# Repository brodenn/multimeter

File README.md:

# 🧪 Arduino Multimeter Project

This is my school project where I designed, built, and programmed a fully functional digital multimeter using an Arduino Uno and a custom PCB designed in KiCad.

📄 [Click here to read the full report (PDF)](docs/P2-Multimeter-Report.pdf)

---

## ✅ Features

- 🟢 **Voltage Measurement**
  - Low voltage: 0–5V (direct to ADC)
  - High voltage: 5–33.7V (via voltage divider)

- 🟠 **Resistance Measurement**
  - Low resistance: 0–1kΩ
  - High resistance: 1–100kΩ

- 🔋 **Battery Monitoring**
  - Detects 9V and 12V sources
  - Provides low battery and no battery warnings

- 🎛️ **Rotary Switch Mode Selection**
  - Modes detected via 4-bit digital input

- 🔊 **Visual & Audio Feedback**
  - Green/Yellow/Red LEDs for status indication
  - Buzzer for continuity and battery alerts

- 🔢 **3-Digit 7-Segment Display**
  - Controlled via CD74HCT4511 BCD driver
  - Efficient multiplexing with decimal control

---

## 📷 Preview

### Schematic

### Top Layer

### Bottom Layer

### PCB Design

### Assembled Multimeter

---

## 🛠️ Tools Used

- Arduino Uno R3
- KiCad 7+
- LTspice (for simulation)
- Fluke multimeter (for verification)
- Soldering station, protoboard, and banana connectors

---

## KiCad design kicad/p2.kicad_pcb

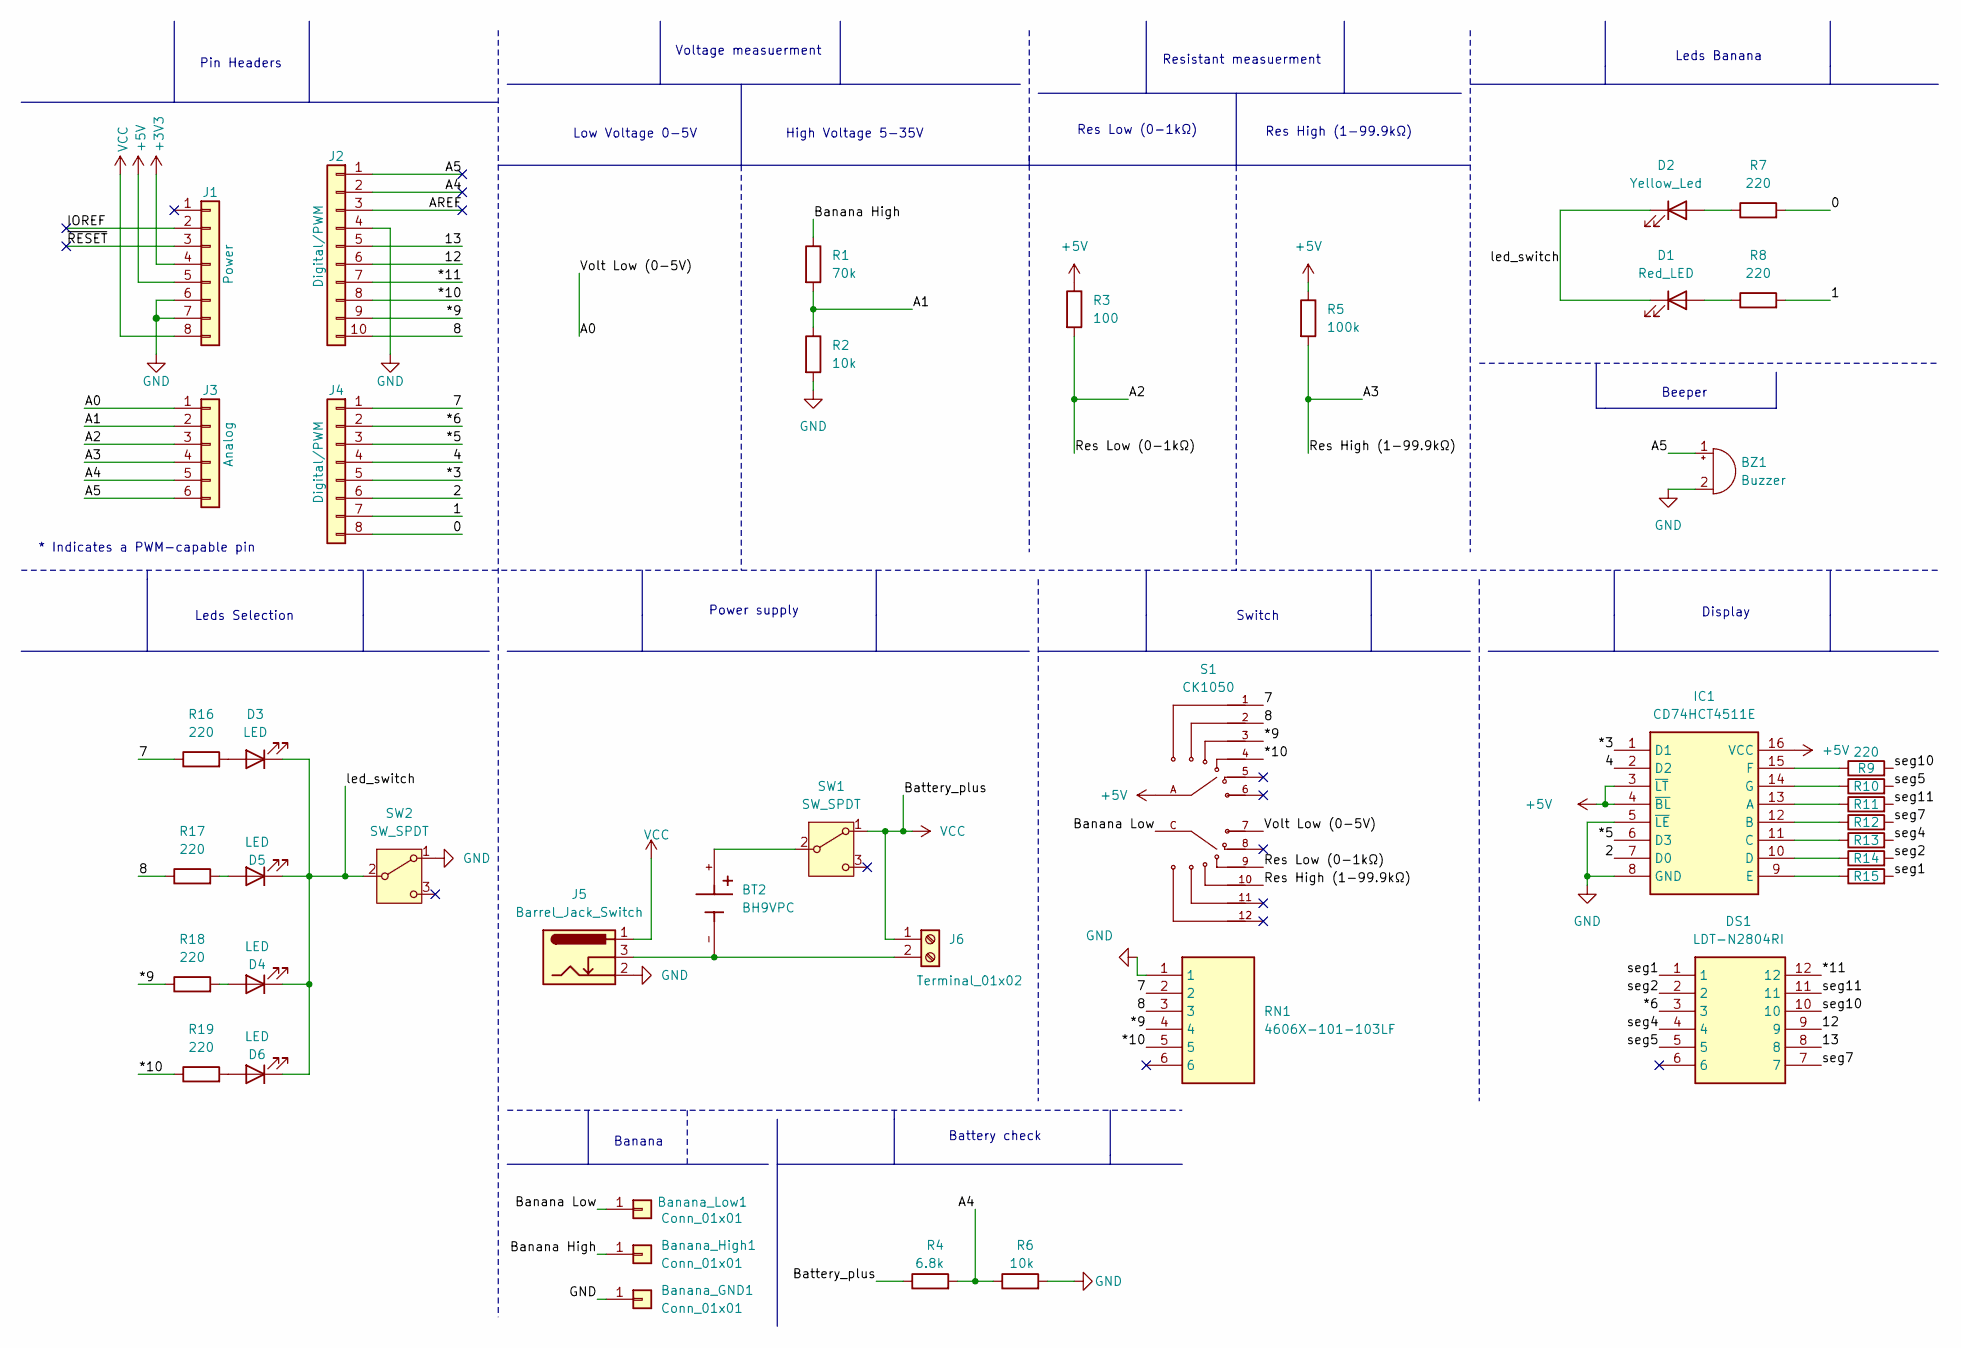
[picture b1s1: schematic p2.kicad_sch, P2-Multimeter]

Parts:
BT2: BH9VPC; BAT_BH9VPC; PARTREV F
BZ1: Buzzer; Buzzer_12x9.5RM7.6
Banana_GND1: Conn_01x01; Banana_Jack_1Pin
Banana_High1: Conn_01x01; Banana_Jack_1Pin
Banana_Low1: Conn_01x01; Banana_Jack_1Pin
D1: Red_LED; LED_D5.0mm
D2: Yellow_Led; LED_D5.0mm
D3, D4, D5, D6: LED; LED_D5.0mm
DS1: LDT-N2804RI; DIPS762W45P254L2253H610Q12N; Mouser Part Number 696-LDT-N2804RI
IC1: CD74HCT4511E; DIP794W53P254L1930H508Q16N; Mouser Part Number 595-CD74HCT4511E
J1: Power; PinSocket_1x08_P2.54mm_Vertical
J2: Digital/PWM; PinSocket_1x10_P2.54mm_Vertical
J3: Analog; PinSocket_1x06_P2.54mm_Vertical
J4: Digital/PWM; PinSocket_1x08_P2.54mm_Vertical
J5: Barrel_Jack_Switch; BarrelJack_Horizontal
J6: Terminal_01x02; terminal_battery
R1: 70k; R_Axial_DIN0207_L6.3mm_D2.5mm_P10.16mm_Horizontal
R2, R6: 10k; R_Axial_DIN0207_L6.3mm_D2.5mm_P10.16mm_Horizontal
R3: 100; R_Axial_DIN0207_L6.3mm_D2.5mm_P10.16mm_Horizontal
R4: 6.8k; R_Axial_DIN0207_L6.3mm_D2.5mm_P10.16mm_Horizontal
R5: 100k; R_Axial_DIN0207_L6.3mm_D2.5mm_P10.16mm_Horizontal
R7, R8, R9, R10, R11, R12, R13, R14, R15, R16, R17, R18, R19: 220; R_Axial_DIN0207_L6.3mm_D2.5mm_P10.16mm_Horizontal
RN1: 4606X-101-103LF; 4606X102103LF; Mouser Part Number 652-4606X-1LF-10K
S1: CK1050; SW_CK1050; PARTREV NA
SW1, SW2: SW_SPDT; SW_Slide-03_Wuerth-WS-SLTV_10x2.5x6.4_P2.54mm

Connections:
+3V3: J1.4
+5V: IC1.3 (~LT), IC1.4 (~BL), IC1.16 (VCC), J1.5, R3.1, R5.1, S1.A
/0: J4.8, R7.2
/1: J4.7, R8.2
/2: IC1.7 (D0), J4.6
/4: IC1.2 (D2), J4.4
/7: J4.1, R16.1, RN1.2, S1.1
/8: J2.10, R17.1, RN1.3, S1.2
/12: DS1.9, J2.6
/13: DS1.8, J2.5
/*3: IC1.1 (D1), J4.5
/*5: IC1.6 (D3), J4.3
/*6: DS1.3, J4.2
/*9: J2.9, R18.1, RN1.4, S1.3
/*10: J2.8, R19.1, RN1.5, S1.4
/*11: DS1.12, J2.7
/A0: J3.1, S1.7
/A1: J3.2, R1.2, R2.1
/A2: J3.3, R3.2, S1.9
/A3: J3.4, R5.2, S1.10
/A4: J2.2, J3.5, R4.2, R6.1
/A5: BZ1.1 (+), J2.1, J3.6
/AREF: J2.3
/Banana High: Banana_High1.1, R1.1
/Banana Low: Banana_Low1.1, S1.C
/IOREF: J1.2
/led_switch: D1.1 (K), D2.1 (K), D3.1 (K), D4.1 (K), D5.1 (K), D6.1 (K), SW2.2 (B)
/seg1: DS1.1, R15.2
/seg2: DS1.2, R14.2
/seg4: DS1.4, R13.2
/seg5: DS1.5, R10.2
/seg7: DS1.7, R12.2
/seg10: DS1.10, R9.2
/seg11: DS1.11, R11.2
/~RESET: J1.3
GND: BZ1.2 (-), Banana_GND1.1, IC1.5 (~LE), IC1.8 (GND), J1.6, J1.7, J2.4, J5.2, R2.2, R6.2, RN1.1, SW2.1 (A)
unnamed: D1.2 (A), R8.1
unnamed: D2.2 (A), R7.1
unnamed: D3.2 (A), R16.2
unnamed: D4.2 (A), R18.2
unnamed: D5.2 (A), R17.2
unnamed: D6.2 (A), R19.2
unnamed: IC1.13 (A), R11.1
unnamed: IC1.12 (B), R12.1
unnamed: IC1.11 (C), R13.1
unnamed: IC1.10 (D), R14.1
unnamed: IC1.9 (E), R15.1
unnamed: IC1.15 (F), R9.1
unnamed: IC1.14 (G), R10.1
unnamed: BT2.-, J5.3, J6.2
unnamed: BT2.+, SW1.2 (B)
VCC: J1.8, J5.1, J6.1, R4.1, SW1.1 (A)

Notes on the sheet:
High Voltage 5-35V
Voltage measuerment
Low Voltage 0-5V
Leds Selection
Display
Beeper
Res High (1-99.9kΩ)
Pin Headers
Banana
Res Low (0-1kΩ)
Leds Banana
Switch
* Indicates a PWM-capable pin
Resistant measuerment
Battery check
Power supply

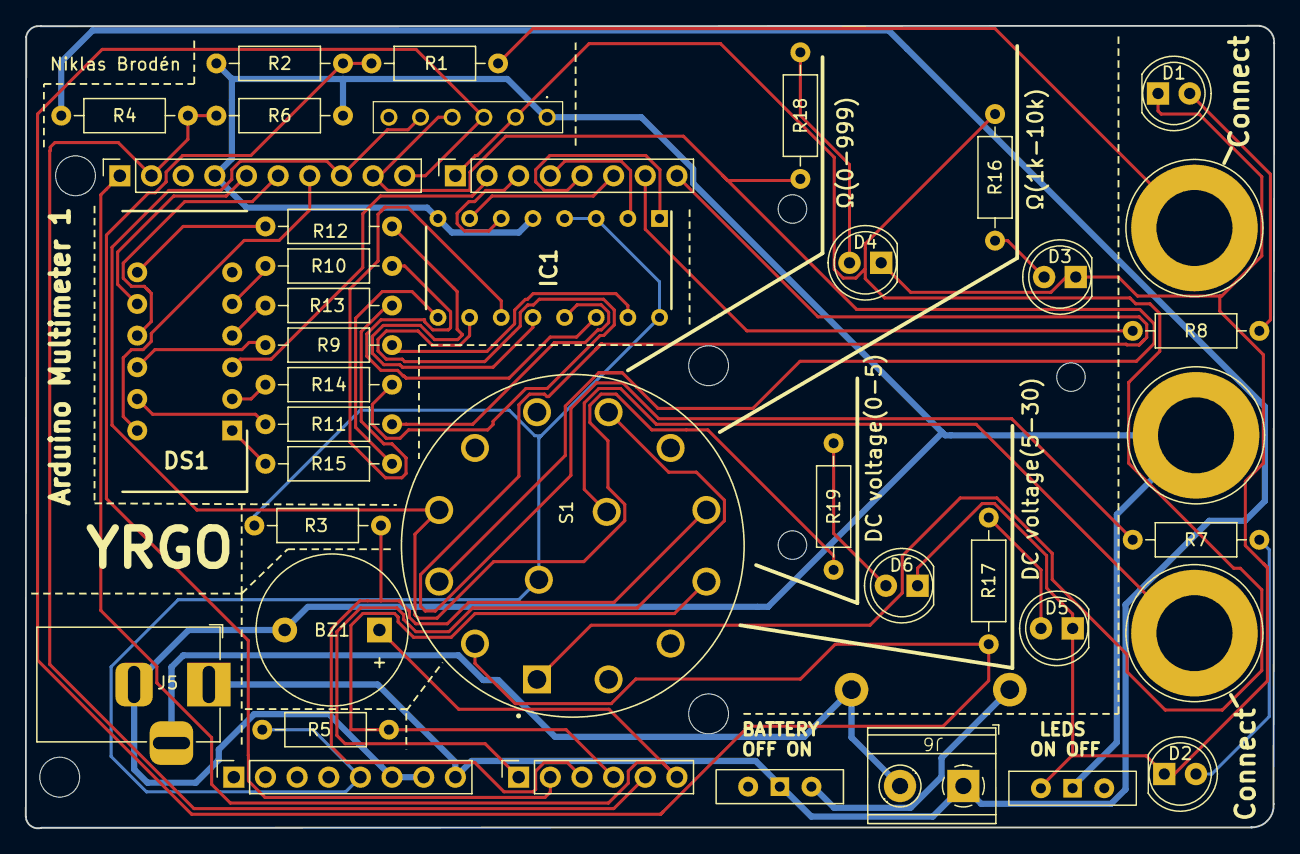
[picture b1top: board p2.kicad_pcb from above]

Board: 2 copper layers, 100.2 x 64.4 mm, 46 parts (1 on the bottom side), 48 nets.

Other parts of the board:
MH1, MH2, MH3, MH4: MountingHole_3.2mm

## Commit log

2025-04-30 Add LDT-N2804RI component library and associated files
    - Created new module file for DIPS762W45P254L2253H610Q12N with detailed footprint and pads.
    - Added documentation files including .dcm, .kicad_sym, .lib, and .mod for LDT-N2804RI.
    - Included part information in part_info.txt and licensing details in license.txt.
    - Ensured all files are properly formatted and contain relevant metadata for integration into KiCad.
2025-05-04 Refactor code structure for improved readability and maintainability
2025-05-04 Update image file extensions in README.md from PNG to JPG
2025-05-04 Improve README.md clarity and consistency by refining descriptions and correcting image file names
2025-05-04 Implement code changes to enhance functionality and improve performance
2025-05-11 Add multimeter functionality with pin assignments and display logic
